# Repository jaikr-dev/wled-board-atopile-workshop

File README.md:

# WLED Board Workshop
## When I Discovered Code-Driven PCB Design

This isn't just another LED controller board. It's the moment I realized PCB design could be as elegant and collaborative as software development.

Built during a workshop with Atopile's founders in San Francisco, this WiFi-enabled LED controller represents a complete paradigm shift: 25 individually addressable RGB LEDs controlled by an ESP32, all designed through code instead of traditional schematic capture. Every component placement, every connection, every design decision expressed in 85 lines of readable, maintainable, Git-trackable code.

## 💡 The Problem I Couldn't Ignore

I've always loved PCB design because it demands creativity and precision in an incredibly constrained environment. PCBs are the invisible backbone of innovation. Literally everything electronic runs off one. But despite this fundamental importance, the tools we use to design them are... frustrating.

Even after getting comfortable with Altium, there's always something breaking. No uniformity in how anyone uses the tools. Endless repetitive work: connecting the same resistor to every LED, manually routing similar circuits over and over. And collaboration? Forget about it. It's nothing like the seamless git workflow we take for granted in software.

The breaking point was realizing I couldn't reuse anything. Every 555 timer circuit, every power supply, every LED driver gets designed from scratch each time, even though they're fundamentally identical. 

That's when I started wondering: "What if PCB design worked like software development?"

## 🔍 What Atopile Actually Changes

This workshop wasn't just about learning a new tool. It was about discovering a completely different way to think about hardware design:

**Modularity**: Design a LED column once, instantiate it five times with `new LEDColumn[5]`.  
**Reusability**: Import someone else's ESP32 module and just use it.  
**Collaboration**: Git commits, pull requests, and merge conflicts... for hardware.  
**Automation**: Built-in assertions catch errors before they become expensive mistakes.  
**Speed**: 10x faster iteration because you're not manually placing and connecting everything.

The magic moment was looking at 85 lines of Atopile code and realizing it completely described a WiFi-enabled LED controller that would have taken me days to design traditionally.

## 🏗️ How It's Actually Built

The elegance is in how everything connects. Here's the complete architecture in 85 lines of code:

### The Modular Approach
```ato
# Five LED columns, each with 5 WS2812B LEDs
led_columns = new LEDColumn[5]

# Power them all with a simple loop
for led_column in led_columns:
    power_5v ~ led_column.power_5v

# Chain the data signals
led_columns[0].data_out ~ led_columns[1].data_in
led_columns[1].data_out ~ led_columns[2].data_in
# ...and so on
```

That's it. No manual component placement, no repetitive connections. Define the pattern once, scale it infinitely.

### The Circuit Reality (It's pretty simple)
- **ESP32-WROOM-32-N4**: WiFi-enabled microcontroller running the show
- **SN74AHCT125PWR**: Level shifter converting 3.3V logic to 5V LED signals  
- **USB-C power**: Clean 5V input with proper decoupling (470µF caps where they belong)
- **100Ω series resistor**: Signal integrity for the data line
- **25 WS2812B LEDs**: Individually addressable RGB pixels in a 5×5 matrix

### Why This Matters Technically
Traditional PCB tools would require manually placing 25 LEDs, drawing 75+ connections, and praying you didn't miss anything. With Atopile, you define a `LEDColumn` module once and instantiate it five times. Change your mind about the LED count? Edit one number. Need different LEDs? Swap the import. Want 10 columns instead of 5? `new LEDColumn[10]`.

## 🛠️ Try It Yourself

Clone this repo and you'll have a working WLED controller in minutes:

```bash
git clone https://github.com/your-username/wled-board-atopile-workshop.git
cd wled-board-atopile-workshop

# Generate the complete board layout
ato build

# Or build just the LED column for testing
ato build led_column
```

**Prerequisites**: [Atopile](https://atopile.io/) 0.9.2+, [KiCad](https://www.kicad.org/) 7.0+, and Git

The real magic happens when you start modifying. Want 10 LED columns instead of 5? Change one line: `led_columns = new LEDColumn[10]`. Need different LEDs? Swap the import in `LEDColumn.ato`. Add sensors? Create new `.ato` modules and import them. 

This is what modular hardware design looks like.

## 📁 Project Structure

```
wled-board-atopile-workshop/
├── main.ato                    # Main WLED controller with ESP32, level shifter, power management
├── LEDColumn.ato              # Reusable LED column module (5 WS2812B LEDs)
├── ato.yaml                   # Atopile project configuration and build targets
├── layouts/                   # Generated KiCad PCB layouts
│   ├── default/              # Complete board layout
│   └── led_column/           # Individual LED column for testing
├── parts/                    # Component libraries with specs and 3D models
│   ├── Espressif_Systems_ESP32_WROOM_32_N4/
│   ├── Texas_Instruments_SN74AHCT125PWR/    # Level shifter
│   ├── XINGLIGHT_XL_5050RGBC_WS2812B/       # RGB LEDs
│   ├── SHOU_HAN_TYPE_C_6P/                  # USB-C connector
│   └── ...                   # Passive components (resistors, capacitors)
├── assembled_boards.jpg      # Final boards in action
├── kicad_3d_model.png       # 3D render
└── workshop_photo.jpeg      # Workshop memories
```

The beauty is in the organization: everything needed for a complete PCB design, from component libraries to 3D models, all version-controlled and shareable.

## 📷 San Francisco Workshop

This board came to life during an incredible weekend in San Francisco. Ioannis and Narayan, Atopile's co-founders, hosted me and two friends while I was in town for Y Combinator's AI Startup School. What struck me wasn't just their technical brilliance, but how genuinely excited they get about solving real problems in hardware design.

The learning curve was real. Switching from visual schematics to thinking about circuits as code took genuine mental rewiring. But watching a complete PCB design emerge from readable, logical code? That moment of understanding felt like discovering a superpower.

## 🔮 What This Actually Enables

Here's what gets me excited about where this is heading:

**Right now**: I can design a functional PCB in the time it used to take me to place components.  
**Soon**: AI will generate working circuit modules from simple prompt.   
**Eventually**: Hardware development becomes as collaborative and fast as software. [Have a look at this LinkedIn post from Ioannis](https://www.linkedin.com/posts/ioannis-papamanoglou_looks-like-llms-can-build-hardware-now-activity-7346651478536646657-VoHD?utm_source=share&utm_medium=member_desktop&rcm=ACoAADRcZ2gB1nHtYN8_9pezp5tOuHOZ3t4stl4).

The bigger picture isn't just faster PCB design. It's bringing hardware development into the same ecosystem of tools, practices, and collaboration that made software development so powerful. When every circuit is a reusable module, when hardware designs can be forked and improved like code, when AI can generate working PCBs from prompts... that changes everything.

## 🙏 Thanks

Massive thanks to Ioannis and Narayan for the incredible workshop and for building something that genuinely changes how we think about hardware design. They're not just improving tools, they're redefining what's possible.

I'm always willing to learn new things if they help me work faster, create better quality, and raise my baseline. Atopile delivers on that promise in ways I didn't think were possible.

---

This isn't just a WLED board. It's proof that the future of hardware design is already here. When I look at these 85 lines of code that completely describe a WiFi-enabled LED controller, I see the same revolutionary potential that transformed software development decades ago.

The paradigm shift is happening. Code-driven hardware is real, and it's incredible.

**License**: Apache 2.0 ([LICENSE.txt](LICENSE.txt))

*P.S. - If you're still wrestling with traditional schematic capture, try Atopile. Your future self will thank you.*

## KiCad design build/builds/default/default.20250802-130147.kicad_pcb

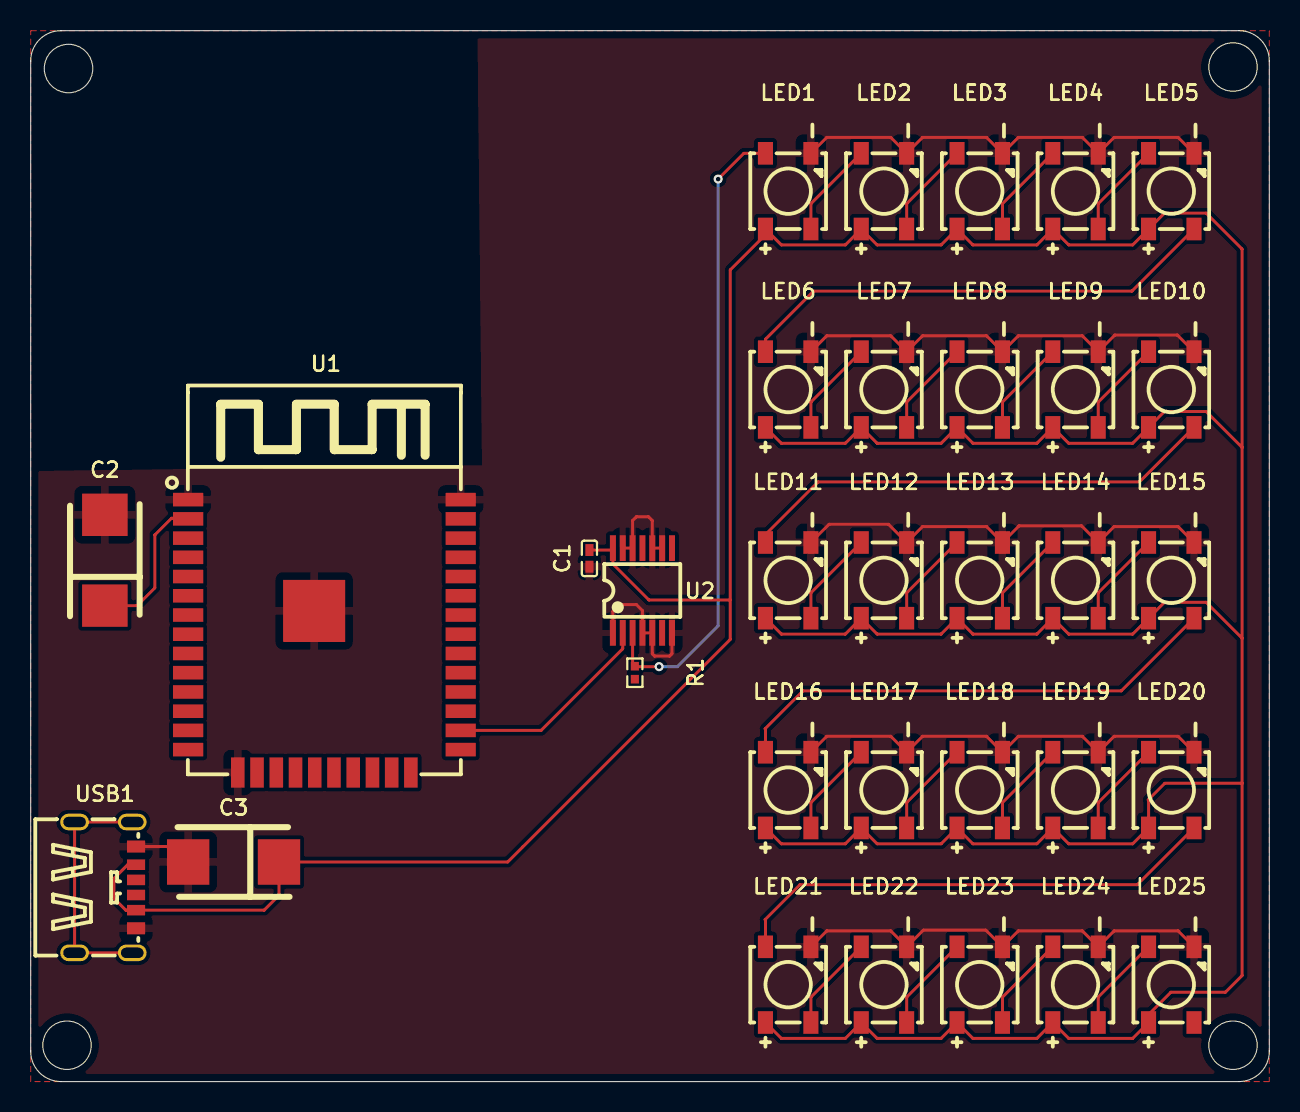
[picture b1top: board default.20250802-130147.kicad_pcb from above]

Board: 2 copper layers, 81.8 x 69.4 mm, 32 parts (0 on the bottom side), 29 nets.

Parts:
C1: 100nF ±10% 16V X7R; C0402
C2, C3: 470µF ±10%; CASE-D_7343
LED1, LED2, LED3, LED4, LED5, LED6, LED7, LED8, LED9, LED10, LED11, LED12, LED13, LED14, LED15, LED16, LED17, LED18, LED19, LED20, LED21, LED22, LED23, LED24, LED25: LED-SMD_4P-L5.0-W5.0-BL_XL-5050RGBC
R1: 100Ω ±1% 62.5mW; R0402
U1: WIFIM-SMD_ESP32-WROOM-32-N4
U2: TSSOP-14_L5.0-W4.4-P0.65-LS6.4-BL
USB1: TYPE-C-SMD_TYPE-C-6P

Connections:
P1A: U1.26, U2.2
P3V3: C2.1, U1.2
VDD: C1.2, C3.1, LED1.1, LED2.1, LED3.1, LED4.1, LED5.1, LED6.1, LED7.1, LED8.1, LED9.1, LED10.1, LED11.1, LED12.1, LED13.1, LED14.1, LED15.1, LED16.1, LED17.1, LED18.1, LED19.1, LED20.1, LED21.1, LED22.1, LED23.1, LED24.1, LED25.1, U2.14, USB1.A9, USB1.B9
data_in: LED5.2, LED6.4
data_in-1: LED20.2, LED21.4
data_in-2: LED1.4, R1.1, U2.3
data_in-3: LED15.2, LED16.4
data_in-4: LED10.2, LED11.4
gnd: C1.1, C2.2, C3.2, LED1.3, LED2.3, LED3.3, LED4.3, LED5.3, LED6.3, LED7.3, LED8.3, LED9.3, LED10.3, LED11.3, LED12.3, LED13.3, LED14.3, LED15.3, LED16.3, LED17.3, LED18.3, LED19.3, LED20.3, LED21.3, LED22.3, LED23.3, LED24.3, LED25.3, U1.1, U1.15, U1.38, U1.39, U2.1, U2.4, U2.5, U2.7, U2.9, U2.10, U2.12, U2.13, USB1.A12, USB1.B12
led_columns[0]-DIN: LED4.2, LED5.4
led_columns[0]-DIN-1: LED3.2, LED4.4
led_columns[0]-DOU: LED1.2, LED2.4
led_columns[0]-DOU-1: LED2.2, LED3.4
led_columns[1]-DIN: LED9.2, LED10.4
led_columns[1]-DOU: LED6.2, LED7.4
led_columns[1]-DOU-1: LED8.2, LED9.4
led_columns[1]-DOU-2: LED7.2, LED8.4
led_columns[2]-DIN: LED12.2, LED13.4
led_columns[2]-DOU: LED14.2, LED15.4
led_columns[2]-DOU-1: LED11.2, LED12.4
led_columns[2]-DOU-2: LED13.2, LED14.4
led_columns[3]-DIN: LED17.2, LED18.4
led_columns[3]-DIN-1: LED19.2, LED20.4
led_columns[3]-DOU: LED18.2, LED19.4
led_columns[3]-DOU-1: LED16.2, LED17.4
led_columns[4]-DIN: LED21.2, LED22.4
led_columns[4]-DOU: LED22.2, LED23.4
led_columns[4]-DOU-1: LED23.2, LED24.4
led_columns[4]-DOU-2: LED24.2, LED25.4

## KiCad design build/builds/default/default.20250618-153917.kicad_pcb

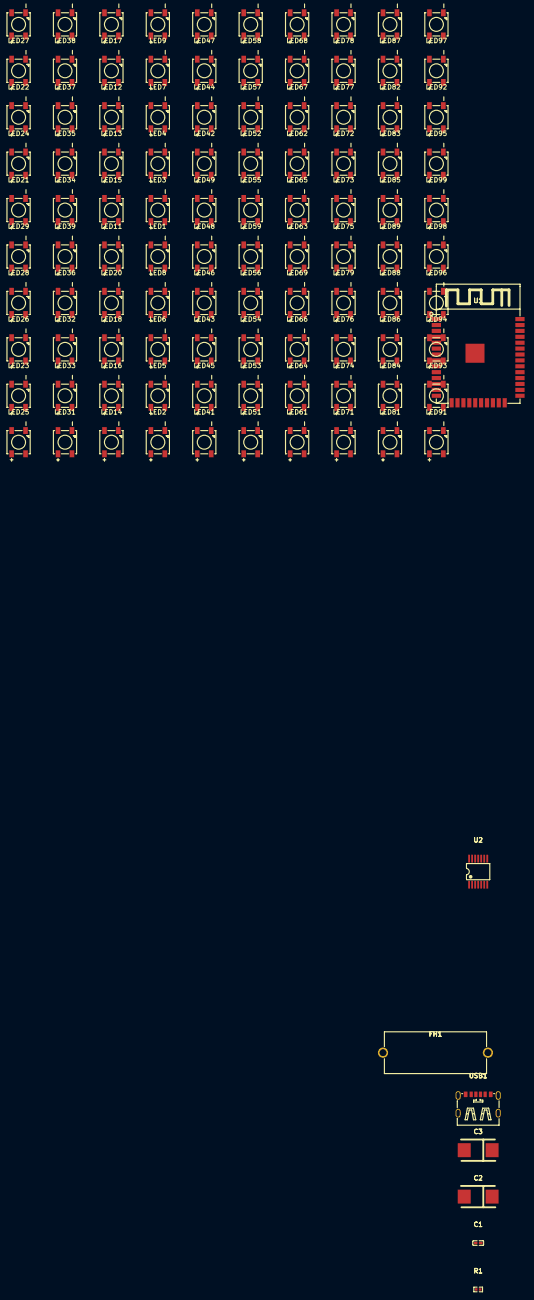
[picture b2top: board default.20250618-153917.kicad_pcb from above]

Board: 2 copper layers, 108 parts (0 on the bottom side), 105 nets, no tracks yet.

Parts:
C1: 100nF ±10% 16V X7R; C0402
C2, C3: 470µF ±10%; CASE-D_7343
FH1: FUSE-TH_L22.0-W9.0-P22.60
LED1, LED2, LED3, LED4, LED5, LED6, LED7, LED8, LED9, LED10, LED11, LED12, LED13, LED14, LED15, LED16, LED17, LED18, LED19, LED20, LED21, LED22, LED23, LED24, LED25, LED26, LED27, LED28, LED29, LED30, LED31, LED32, LED33, LED34, LED35, LED36, LED37, LED38, LED39, LED40, LED41, LED42, LED43, LED44, LED45, LED46, LED47, LED48, LED49, LED50, LED51, LED52, LED53, LED54, LED55, LED56, LED57, LED58, LED59, LED60, LED61, LED62, LED63, LED64, LED65, LED66, LED67, LED68, LED69, LED70, LED71, LED72, LED73, LED74, LED75, LED76, LED77, LED78, LED79, LED80, LED81, LED82, LED83, LED84, LED85, LED86, LED87, LED88, LED89, LED90, LED91, LED92, LED93, LED94, LED95, LED96, LED97, LED98, LED99, LED100: LED-SMD_4P-L5.0-W5.0-BL_XL-5050RGBC
R1: 100Ω ±1% 62.5mW; R0402
U1: WIFIM-SMD_ESP32-WROOM-32-N4
U2: TSSOP-14_L5.0-W4.4-P0.65-LS6.4-BL
USB1: TYPE-C-SMD_TYPE-C-6P

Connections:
P1A: U1.26, U2.2
P1Y: LED1.4, R1.1, U2.3
P3V3: C2.2, U1.2
VCC: C1.2, FH1.2, U2.14
VDD: C3.2, FH1.1, LED1.1, LED2.1, LED3.1, LED4.1, LED5.1, LED6.1, LED7.1, LED8.1, LED9.1, LED10.1, LED11.1, LED12.1, LED13.1, LED14.1, LED15.1, LED16.1, LED17.1, LED18.1, LED19.1, LED20.1, LED21.1, LED22.1, LED23.1, LED24.1, LED25.1, LED26.1, LED27.1, LED28.1, LED29.1, LED30.1, LED31.1, LED32.1, LED33.1, LED34.1, LED35.1, LED36.1, LED37.1, LED38.1, LED39.1, LED40.1, LED41.1, LED42.1, LED43.1, LED44.1, LED45.1, LED46.1, LED47.1, LED48.1, LED49.1, LED50.1, LED51.1, LED52.1, LED53.1, LED54.1, LED55.1, LED56.1, LED57.1, LED58.1, LED59.1, LED60.1, LED61.1, LED62.1, LED63.1, LED64.1, LED65.1, LED66.1, LED67.1, LED68.1, LED69.1, LED70.1, LED71.1, LED72.1, LED73.1, LED74.1, LED75.1, LED76.1, LED77.1, LED78.1, LED79.1, LED80.1, LED81.1, LED82.1, LED83.1, LED84.1, LED85.1, LED86.1, LED87.1, LED88.1, LED89.1, LED90.1, LED91.1, LED92.1, LED93.1, LED94.1, LED95.1, LED96.1, LED97.1, LED98.1, LED99.1, LED100.1, USB1.A9, USB1.B9
data_in: LED90.2, LED91.4
data_in-1: LED10.2, LED11.4
data_in-2: LED80.2, LED81.4
data_in-3: LED30.2, LED31.4
data_out: LED50.2, LED51.4
data_out-1: LED60.2, LED61.4
data_out-2: LED20.2, LED21.4
data_out-3: LED40.2, LED41.4
data_out-4: LED70.2, LED71.4
gnd: C1.1, C2.1, C3.1, LED1.3, LED2.3, LED3.3, LED4.3, LED5.3, LED6.3, LED7.3, LED8.3, LED9.3, LED10.3, LED11.3, LED12.3, LED13.3, LED14.3, LED15.3, LED16.3, LED17.3, LED18.3, LED19.3, LED20.3, LED21.3, LED22.3, LED23.3, LED24.3, LED25.3, LED26.3, LED27.3, LED28.3, LED29.3, LED30.3, LED31.3, LED32.3, LED33.3, LED34.3, LED35.3, LED36.3, LED37.3, LED38.3, LED39.3, LED40.3, LED41.3, LED42.3, LED43.3, LED44.3, LED45.3, LED46.3, LED47.3, LED48.3, LED49.3, LED50.3, LED51.3, LED52.3, LED53.3, LED54.3, LED55.3, LED56.3, LED57.3, LED58.3, LED59.3, LED60.3, LED61.3, LED62.3, LED63.3, LED64.3, LED65.3, LED66.3, LED67.3, LED68.3, LED69.3, LED70.3, LED71.3, LED72.3, LED73.3, LED74.3, LED75.3, LED76.3, LED77.3, LED78.3, LED79.3, LED80.3, LED81.3, LED82.3, LED83.3, LED84.3, LED85.3, LED86.3, LED87.3, LED88.3, LED89.3, LED90.3, LED91.3, LED92.3, LED93.3, LED94.3, LED95.3, LED96.3, LED97.3, LED98.3, LED99.3, LED100.3, U1.1, U1.15, U1.38, U1.39, U2.1, U2.4, U2.5, U2.7, U2.9, U2.10, U2.12, U2.13, USB1.A12, USB1.B12
led_columns[0]-DIN: LED2.2, LED3.4
led_columns[0]-DIN-1: LED9.2, LED10.4
led_columns[0]-DIN-2: LED8.2, LED9.4
led_columns[0]-DIN-3: LED4.2, LED5.4
led_columns[0]-DIN-4: LED6.2, LED7.4
led_columns[0]-DOU: LED3.2, LED4.4
led_columns[0]-DOU-1: LED5.2, LED6.4
led_columns[0]-DOU-2: LED7.2, LED8.4
led_columns[0]-DOU-3: LED1.2, LED2.4
led_columns[1]-DIN: LED18.2, LED19.4
led_columns[1]-DIN-1: LED12.2, LED13.4
led_columns[1]-DIN-2: LED14.2, LED15.4
led_columns[1]-DIN-3: LED16.2, LED17.4
led_columns[1]-DOU: LED19.2, LED20.4
led_columns[1]-DOU-1: LED11.2, LED12.4
led_columns[1]-DOU-2: LED15.2, LED16.4
led_columns[1]-DOU-3: LED13.2, LED14.4
led_columns[1]-DOU-4: LED17.2, LED18.4
led_columns[2]-DIN: LED23.2, LED24.4
led_columns[2]-DIN-1: LED29.2, LED30.4
led_columns[2]-DIN-2: LED26.2, LED27.4
led_columns[2]-DOU: LED22.2, LED23.4
led_columns[2]-DOU-1: LED25.2, LED26.4
led_columns[2]-DOU-2: LED21.2, LED22.4
led_columns[2]-DOU-3: LED28.2, LED29.4
led_columns[2]-DOU-4: LED24.2, LED25.4
led_columns[2]-DOU-5: LED27.2, LED28.4
led_columns[3]-DIN: LED36.2, LED37.4
led_columns[3]-DIN-1: LED33.2, LED34.4
led_columns[3]-DIN-2: LED37.2, LED38.4
led_columns[3]-DIN-3: LED32.2, LED33.4
led_columns[3]-DIN-4: LED39.2, LED40.4
led_columns[3]-DOU: LED35.2, LED36.4
led_columns[3]-DOU-1: LED34.2, LED35.4
led_columns[3]-DOU-2: LED31.2, LED32.4
led_columns[3]-DOU-3: LED38.2, LED39.4
led_columns[4]-DIN: LED41.2, LED42.4
led_columns[4]-DIN-1: LED49.2, LED50.4
led_columns[4]-DIN-2: LED43.2, LED44.4
led_columns[4]-DIN-3: LED46.2, LED47.4
led_columns[4]-DIN-4: LED48.2, LED49.4
led_columns[4]-DOU: LED45.2, LED46.4
led_columns[4]-DOU-1: LED42.2, LED43.4
led_columns[4]-DOU-2: LED44.2, LED45.4
led_columns[4]-DOU-3: LED47.2, LED48.4
led_columns[5]-DIN: LED58.2, LED59.4
led_columns[5]-DIN-1: LED51.2, LED52.4
led_columns[5]-DIN-2: LED59.2, LED60.4
led_columns[5]-DIN-3: LED56.2, LED57.4
led_columns[5]-DOU: LED53.2, LED54.4
led_columns[5]-DOU-1: LED52.2, LED53.4
led_columns[5]-DOU-2: LED54.2, LED55.4
led_columns[5]-DOU-3: LED55.2, LED56.4
led_columns[5]-DOU-4: LED57.2, LED58.4
led_columns[6]-DIN: LED69.2, LED70.4
led_columns[6]-DIN-1: LED66.2, LED67.4
led_columns[6]-DIN-2: LED63.2, LED64.4
led_columns[6]-DIN-3: LED61.2, LED62.4
led_columns[6]-DIN-4: LED62.2, LED63.4
led_columns[6]-DIN-5: LED68.2, LED69.4
led_columns[6]-DOU: LED64.2, LED65.4
led_columns[6]-DOU-1: LED67.2, LED68.4
led_columns[6]-DOU-2: LED65.2, LED66.4
led_columns[7]-DIN: LED72.2, LED73.4
led_columns[7]-DIN-1: LED79.2, LED80.4
led_columns[7]-DIN-2: LED78.2, LED79.4
led_columns[7]-DIN-3: LED76.2, LED77.4
led_columns[7]-DOU: LED75.2, LED76.4
led_columns[7]-DOU-1: LED77.2, LED78.4
led_columns[7]-DOU-2: LED74.2, LED75.4
led_columns[7]-DOU-3: LED73.2, LED74.4
led_columns[7]-DOU-4: LED71.2, LED72.4
led_columns[8]-DIN: LED88.2, LED89.4
led_columns[8]-DIN-1: LED81.2, LED82.4
led_columns[8]-DIN-2: LED84.2, LED85.4
led_columns[8]-DIN-3: LED82.2, LED83.4
led_columns[8]-DIN-4: LED86.2, LED87.4
led_columns[8]-DOU: LED87.2, LED88.4
led_columns[8]-DOU-1: LED89.2, LED90.4
led_columns[8]-DOU-2: LED85.2, LED86.4
led_columns[8]-DOU-3: LED83.2, LED84.4
led_columns[9]-DIN: LED94.2, LED95.4
led_columns[9]-DIN-1: LED97.2, LED98.4
led_columns[9]-DOU: LED99.2, LED100.4
led_columns[9]-DOU-1: LED95.2, LED96.4
led_columns[9]-DOU-2: LED91.2, LED92.4
led_columns[9]-DOU-3: LED92.2, LED93.4
led_columns[9]-DOU-4: LED93.2, LED94.4
led_columns[9]-DOU-5: LED98.2, LED99.4
led_columns[9]-DOU-6: LED96.2, LED97.4

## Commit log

2025-06-18 Track parts directory and its contents
2025-06-18 Track build directory and its contents
2025-06-18 Remove the 5A fuse
2025-06-18 Add final board version
2025-06-19 Remove build directory
2025-06-19 remove autogenerated trait, fix fp-lib-table, update gitignore
2025-06-19 Formatting
2025-08-02 Create LICENSE
2025-08-02 Update LICENSE
2025-08-02 Add pictures from the workshop
2025-08-02 Add README.md
